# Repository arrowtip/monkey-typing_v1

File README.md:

# monkey_typing V1

## Setup
Install ergogen cli:
```bash
$ npm i ergogen
```

## Usage
To compile the ergogen config into an (unrouted) KiCad PCB run
```bash
$ cd ergogen/
$ make
```
This will create a KiCad PCB under `ergogen/output/pcbs/monkey-typing_v1.kicad_pcb`.
Then copy this file to another location for routing.
Prerouted versions of the keyboard can be found in `kicad/`.

## Build
### Parts
- [3D-printable case](https://cad.onshape.com/documents/ed0d6a4fe642353b2203faf0/w/5ff3ead430589bfdb49bdc3b/e/f0c0ddc8bc3d8364728c5712)
- [3D-printable switch plate](https://cad.onshape.com/documents/5edfe701ad9f2b4f2a2a6781/w/f609051c12ccf6833f78234f/e/c55f49f04b746962ac1a3068)
- 58 diodes (e.g. 1N48)
- 56 mx-style switches
- mx-style keycaps
- rotary encoder (e.g. KY-040)
- 2 through-hole reset buttons
- 2 TRRS jacks TRRS-PJ-320A
- TRRS cable
- 4 6.8 kOhm resistors
- 6 WS2812B or SK6812 LEDs
- 2 microcontrollers (pro-micro or elite-c)

### Assembly
The RGB diodes are hard to hand solder, so using reflow soldering here is 
recommended.

Add two small drops of solder to the three-way jumpers below the microcontroller
on each side to connect the i2c SDA line/GND from the TRRS jack to the 
microcontroller.

Snapping the PCB into the 3D printed case might require a bit of force.
Solder all components before inserting the PCB into the case,
as removing the PCB again from the case might be difficult.

> [!CAUTION]
> Never plug the TRRS cable in or out while the keyboard is connected via USB!

### Firmware
Flash the [QMK firmware](https://github.com/arrowtip/monkey-typing_qmk) to the microcontrollers on both sides.

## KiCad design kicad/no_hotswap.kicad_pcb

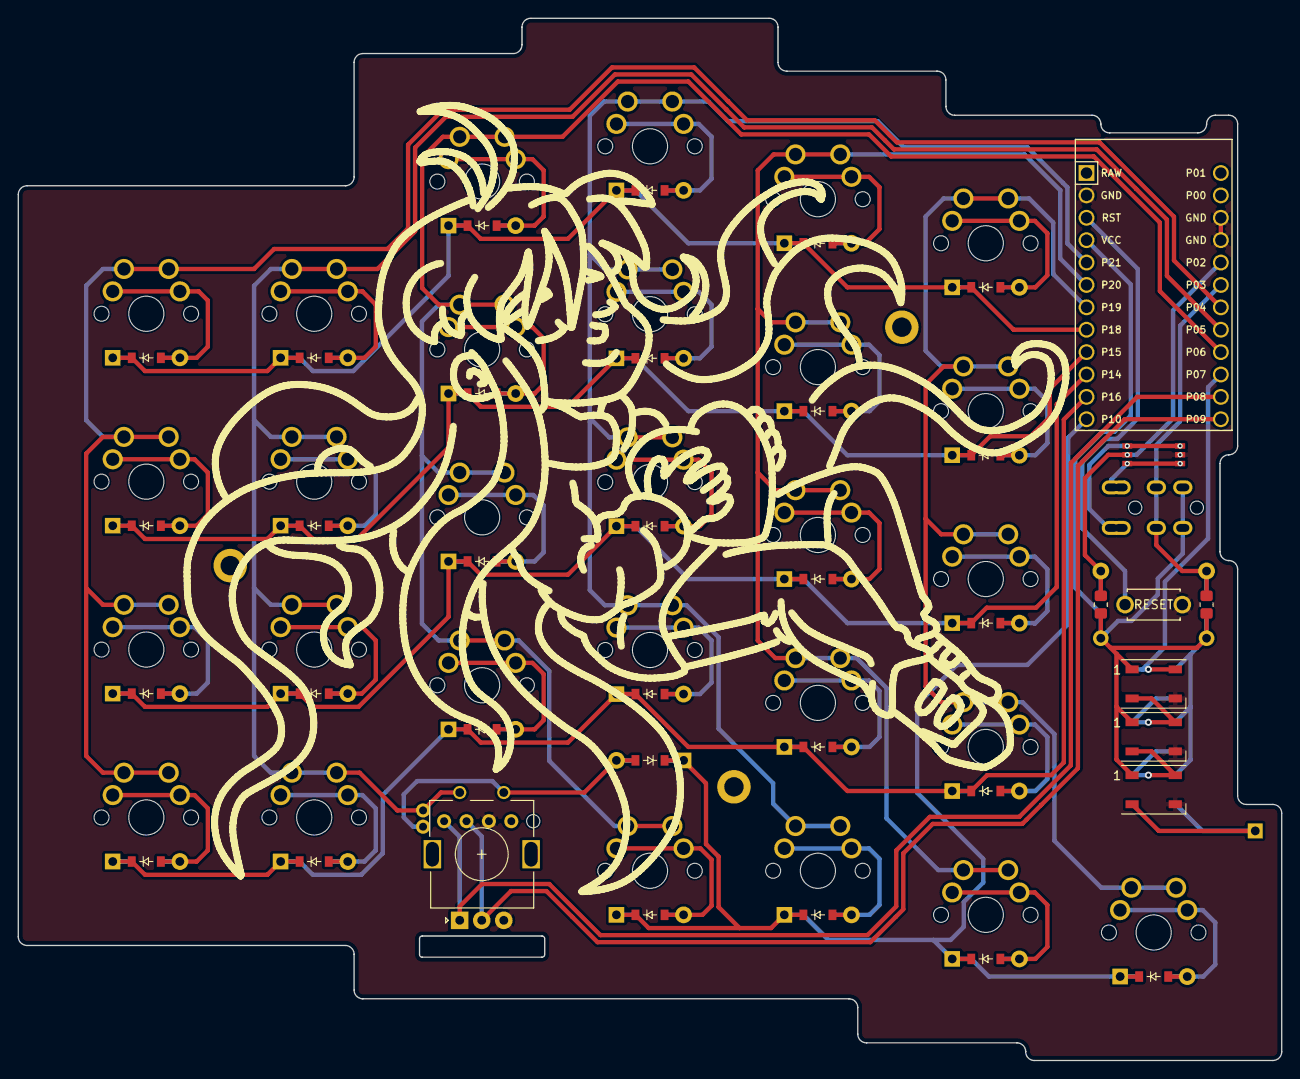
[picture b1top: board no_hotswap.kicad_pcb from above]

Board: 2 copper layers, 143.3 x 118.2 mm, 68 parts (0 on the bottom side), 49 nets.

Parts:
D1, D2, D3, D4, D5, D6, D7, D8, D9, D10, D11, D12, D13, D14, D15, D16, D17, D18, D19, D20, D21, D22, D23, D24, D25, D26, D27, D28, D29: ComboDiode
Ju31, Ju32: Jumper; threeway_jumper
MCU1: ProMicro
R1, R2: ComboResistor
ROT1: rotary_encoder
S1, S2, S3, S4, S5, S6, S7, S8, S9, S10, S11, S12, S13, S14, S15, S16, S17, S18, S19, S20, S21, S22, S23, S24, S25, S26, S27, S28: MX
TRRS1: TRRS-PJ-320A-dual
_1: ResetSW
_2, _3, _4: MountingHole_2.2mm_M2

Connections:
GND: Ju32.2, Ju32.5, MCU1.2, MCU1.15, MCU1.16, ROT1.B, _1.2
P2: Ju31.2, Ju31.5, MCU1.17, R1.2
P3: MCU1.18, R2.2, TRRS1.3
P4: MCU1.19, S1.1, S2.1, S3.1, S4.1
P5: MCU1.20, ROT1.1, S5.1, S6.1, S7.1, S8.1
P6: MCU1.21, S9.1, S10.1, S11.1, S12.1, S25.1
P8: MCU1.23, ROT1.A
P9: MCU1.24, ROT1.C
P10: D25.1, D26.1, D27.1, D28.1, D29.1, MCU1.12
P14: D2.1, D6.1, D10.1, D14.1, D18.1, D22.1, MCU1.10
P15: D3.1, D7.1, D11.1, D15.1, D19.1, D23.1, MCU1.9
P16: D1.1, D5.1, D9.1, D13.1, D17.1, D21.1, MCU1.11
P18: D4.1, D8.1, D12.1, D16.1, D20.1, D24.1, MCU1.8
P19: MCU1.7, S21.1, S22.1, S23.1, S24.1, S28.1
P20: MCU1.6, S17.1, S18.1, S19.1, S20.1, S27.1
P21: MCU1.5, S13.1, S14.1, S15.1, S16.1, S26.1
RST: MCU1.3, _1.1
VCC: MCU1.4, R1.1, R2.1, TRRS1.4
far_thumb: D27.2, S27.2
farfar_thumb: D28.2, S28.2
home_thumb: D26.2, S26.2
index_bottom: D17.2, S17.2
index_home: D18.2, S18.2
index_num: D20.2, S20.2
index_top: D19.2, S19.2
inner_bottom: D21.2, S21.2
inner_home: D22.2, S22.2
inner_num: D24.2, S24.2
inner_top: D23.2, S23.2
middle_bottom: D13.2, S13.2
middle_home: D14.2, S14.2
middle_num: D16.2, S16.2
middle_top: D15.2, S15.2
my_col_row: D29.2, ROT1.2
near_thumb: D25.2, S25.2
outer_bottom: D1.2, S1.2
outer_home: D2.2, S2.2
outer_num: D4.2, S4.2
outer_top: D3.2, S3.2
pinky_bottom: D5.2, S5.2
pinky_home: D6.2, S6.2
pinky_num: D8.2, S8.2
pinky_top: D7.2, S7.2
ring_bottom: D9.2, S9.2
ring_home: D10.2, S10.2
ring_num: D12.2, S12.2
ring_top: D11.2, S11.2
trrs_gnd: Ju31.3, Ju31.6, Ju32.3, Ju32.6, TRRS1.1
trrs_sda: Ju31.1, Ju31.4, Ju32.1, Ju32.4, TRRS1.2

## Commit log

2024-09-20 start config
2024-09-21 add ergogen
2024-09-23 add indents to protect ports
2024-09-23 add i2c connection hardware
2024-09-24 add scrollwheel and rotary encoder
2024-09-25 pretty sure ws2812 footprint is broken
2024-10-01 fix rgb footprint
2024-10-02 fix trrs symmetric problem
2024-10-02 add mounting holes
2024-10-02 change routing setup for big, beafy tracks!!
2024-10-10 start experimenting with svg graphics
2024-10-12 add madeline to silkscreen
2024-10-13 improve madeline
2024-10-13 add winged berry
2024-10-15 add propper vias to three way jumper
2024-10-15 fix trrs jack
2024-10-19 increase hole diameter for low profile sockets
2024-10-19 start routing
2024-10-19 routing done. silkscreen still needs attention
2024-10-19 fix silkscreen
2024-11-04 add switch plate
2025-01-16 add prerouted mx-style key switch footprint
2025-01-17 add stl for switch plate
2025-01-17 add proper scale and positioning to silkscreen art
    closes #3
2025-01-19 add version number to PCB
    closes #5
2025-01-19 add silkscreen on both sides for resistors and 3-way jumper
    closes #6
    closes #7
2025-01-25 round ws2812 pads
    closes #4
2025-01-25 fix silkscreen of micro controller
    closes #1
2025-01-26 add propper readme
2025-02-03 fix link to firmware repo in readme
2025-03-04 move footprints into separate repository
2025-04-15 fix pre-routed key switches
